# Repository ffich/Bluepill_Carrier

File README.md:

# BluePill Experimental Carrier

🧪 **BluePill Experimental Carrier** is a carrier board designed for development, testing, and rapid experimentation with the **STM32 Blue Pill (STM32F103)**.

The goal of this board is to provide a **feature-rich development platform** with integrated peripherals, industrial communication interfaces, and expansion sockets, while keeping the design clean, educational, and easy to extend.

---

## ✨ Key Features

### On-board Peripherals
- 14 × Status / debug LEDs  
- 3 × User buttons  
- 1 × Wake-up button  
- 1 × Analog potentiometer  
- **TMP102** I2C temperature sensor  
- **I²C OLED** display  
- **SPI EEPROM**  

### Communications
- **CAN bus TJA1051T3** transceiver
- **LIN Bus TJA1029T** transceiver (Configurable Master/Slave)
- **RS-485** interface with dedicated transceiver
- **USB / Serial** interface

### Security
- **Microchip ATECC608C** Cryptographic coprocessor

### Expansion Sockets
- External **DS3231 RTC Breakout** socket  
- **BME280** environmental sensor socket  

---

## 🎯 Design Philosophy

- Built for **experimentation, prototyping, and hardware/software testing**
- Well suited for:
  - Embedded development
  - Industrial and automotive communications (CAN, LIN, RS-485)
  - Sensor integration
  - Industrial and IoT applications
  - Cybersecurity

---

## 🧩 Target Audience

- Advanced makers  
- Electronics / embedded students  
- STM32 firmware developers  
- Educational labs and R&D teams  

---

## ⚠️ Disclaimer

This board is **experimental by design**.  
Layout, features, and routing may evolve as the project progresses and new tests are performed.

---

## 📜 License

Hardware and documentation are released under an open-source license.  
See the `LICENSE` file for details.

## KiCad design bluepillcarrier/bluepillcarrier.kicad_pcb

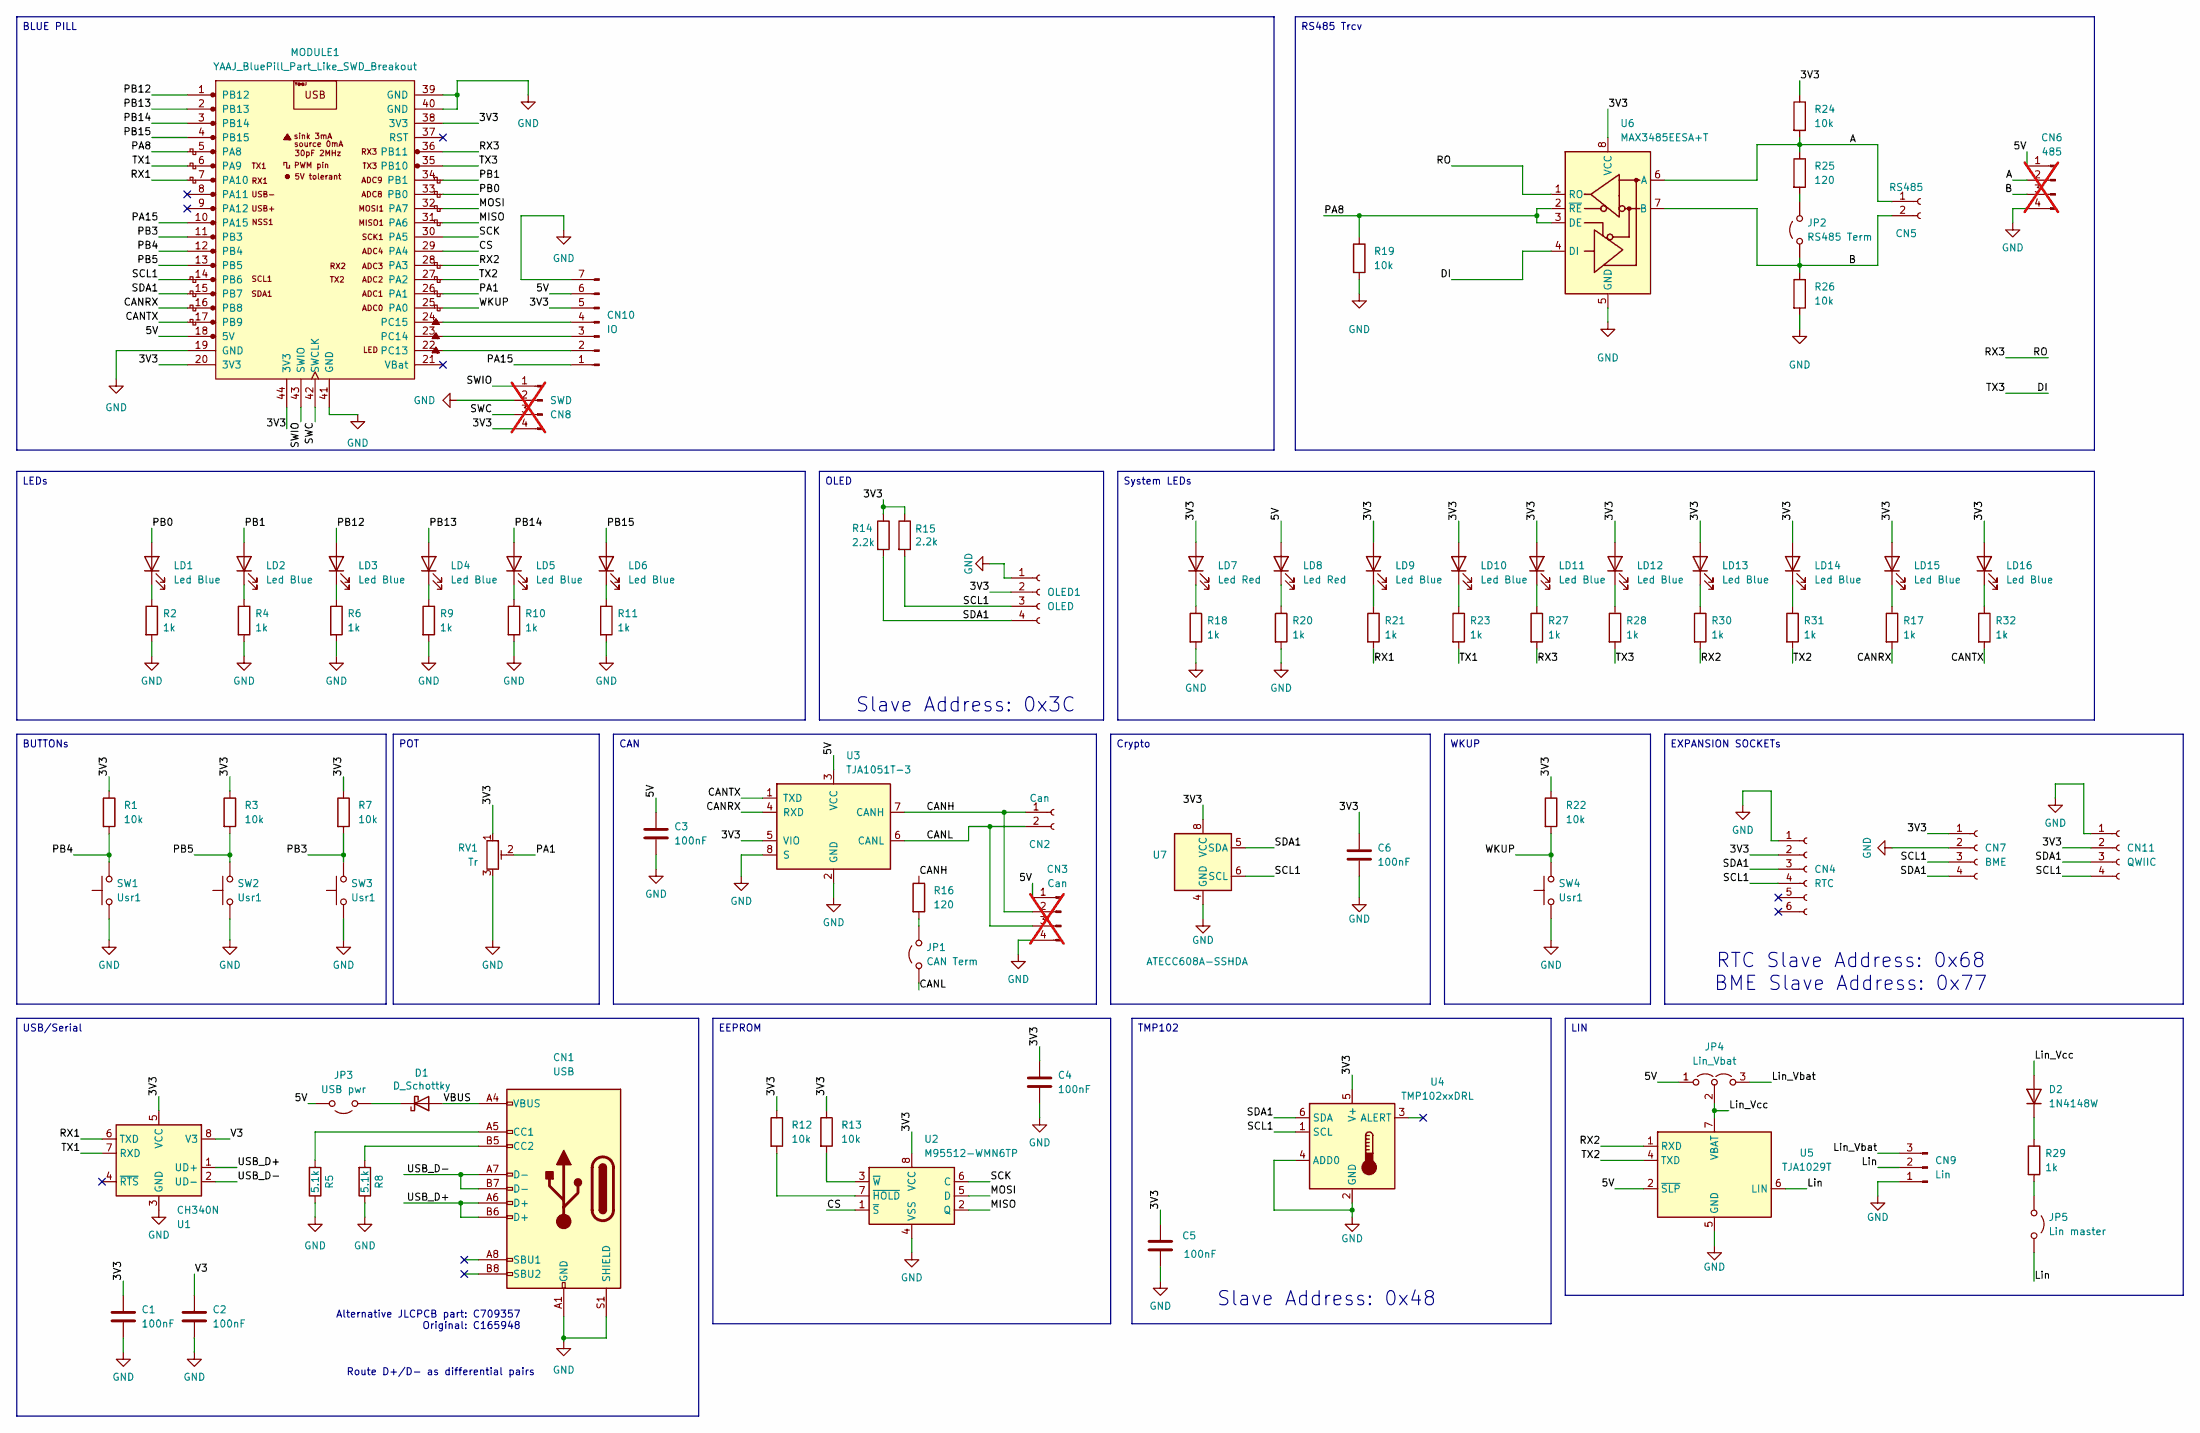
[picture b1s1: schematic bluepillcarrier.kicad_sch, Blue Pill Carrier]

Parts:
C1, C2, C3, C4, C5, C6: 100nF; C_0402_1005Metric; LCSC C155422
CN1: USB; USB_C_Receptacle_HRO_TYPE-C-31-M-12; LCSC C165948
CN2: Can; PhoenixContact_MSTBA_2,5_2-G-5,08_1x02_P5.08mm_Horizontal; LCSC C441204
CN3: Can; PinHeader_1x04_P2.54mm_Vertical; LCSC C2905435; not fitted
CN4: RTC; PinSocket_1x06_P2.54mm_Vertical; LCSC C2832269
CN5: RS485; PhoenixContact_MSTBA_2,5_2-G-5,08_1x02_P5.08mm_Horizontal; LCSC C441204
CN6: 485; PinHeader_1x04_P2.54mm_Vertical; LCSC C2905435; not fitted
CN7: BME; PinSocket_1x04_P2.54mm_Vertical; LCSC C2718488
CN8: SWD; PinHeader_1x04_P2.54mm_Vertical; not fitted
CN9: Lin; PinHeader_1x03_P2.54mm_Vertical; LCSC C49257
CN10: IO; PinSocket_1x07_P2.54mm_Vertical; LCSC C22438157
CN11: QWIIC; JST_SH_SM04B-SRSS-TB_1x04-1MP_P1.00mm_Horizontal; LCSC C160404
D1: D_Schottky; D_SMA; LCSC C412514
D2: 1N4148W; D_SOD-123; LCSC C2099
JP1: CAN Term; PinHeader_1x02_P2.54mm_Vertical; LCSC C5360898
JP2: RS485 Term; PinHeader_1x02_P2.54mm_Vertical; LCSC C5360898
JP3: USB pwr; PinHeader_1x02_P2.54mm_Vertical; LCSC C5360898
JP4: Lin_Vbat; PinHeader_1x03_P2.54mm_Vertical; LCSC C49257
JP5: Lin master; PinHeader_1x02_P2.54mm_Vertical; LCSC C5360898
LD1, LD2, LD3, LD4, LD5, LD6, LD9, LD10, LD11, LD12, LD13, LD14, LD15, LD16: Led Blue; LED_0603_1608Metric; LCSC C2288
LD7, LD8: Led Red; LED_0603_1608Metric; LCSC C2286
MODULE1: YAAJ_BluePill_Part_Like_SWD_Breakout; YAAJ_BluePill_SWD_1; LCSC C2905423
OLED1: OLED; MODULE_DM-OLED096-636; LCSC C5248080
R1, R3, R7, R12, R13, R19, R22, R24, R26: 10k; R_0402_1005Metric; LCSC C174175
R2, R4, R6, R9, R10, R11, R17, R18, R20, R21, R23, R27, R28, R29, R30, R31, R32: 1k; R_0402_1005Metric; LCSC C140196
R5, R8: 5.1k; R_0402_1005Metric; LCSC C25905
R14, R15: 2.2k; R_0603_1608Metric
R16, R25: 120; R_0603_1608Metric; LCSC C177328
RV1: Tr; Potentiometer_Bourns_3386P_Vertical; LCSC C116303
SW1, SW2, SW3, SW4: Usr1; SW_SPST_PTS810; LCSC C221895
U1: CH340N; JEITA_SOIC-8_3.9x4.9mm_P1.27mm; LCSC C2977777
U2: M95512-WMN6TP; SOIC-8_3.9x4.9mm_P1.27mm; LCSC C7567
U3: TJA1051T-3; SOIC-8_3.9x4.9mm_P1.27mm; LCSC C38695
U4: TMP102xxDRL; SOT-563; LCSC C99269
U5: TJA1029T; SOIC-8_3.9x4.9mm_P1.27mm; LCSC C194435
U6: MAX3485EESA+T; SOIC-8_3.9x4.9mm_P1.27mm; LCSC C9943
U7: ATECC608A-SSHDA; SOIC-8_3.9x4.9mm_P1.27mm; LCSC C28975195

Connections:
/3V3: C1.1, C4.1, C5.1, C6.1, CN4.2, CN7.1, CN8.4, CN10.5, CN11.2, LD7.2 (A), LD9.2 (A), LD10.2 (A), LD11.2 (A), LD12.2 (A), LD13.2 (A), LD14.2 (A), LD15.2 (A), LD16.2 (A), MODULE1.20 (3V3), MODULE1.38 (3V3), MODULE1.44 (3V3), OLED1.2, R1.1, R3.1, R7.1, R12.1, R13.1, R14.1, R15.1, R22.1, R24.1, RV1.1, U1.5 (VCC), U2.8 (VCC), U3.5 (VIO), U4.5 (V+), U6.8 (VCC), U7.8 (VCC)
/5V: C3.1, CN3.1, CN6.1, CN10.6, JP3.2 (B), JP4.1 (A), LD8.2 (A), MODULE1.18 (5V), U3.3 (VCC), U5.2 (~SLP)
/A: CN5.1, CN6.2, R24.2, R25.1, U6.6 (A)
/B: CN5.2, CN6.3, JP2.1 (A), R26.1, U6.7 (B)
/CANH: CN2.1, CN3.2, R16.1, U3.7 (CANH)
/CANL: CN2.2, CN3.3, JP1.1 (A), U3.6 (CANL)
/CANRX: MODULE1.16 (PB8), R17.2, U3.4 (RXD)
/CANTX: MODULE1.17 (PB9), R32.2, U3.1 (TXD)
/CS: MODULE1.29 (PA4), U2.1 (~S)
/DI: MODULE1.35 (PB10), R28.2, U6.4 (DI)
/Lin: CN9.2, JP5.2 (B), U5.6 (LIN)
/Lin_Vbat: CN9.3, JP4.3 (B)
/Lin_Vcc: D2.2 (A), JP4.2 (C), U5.7 (VBAT)
/MISO: MODULE1.31 (PA6), U2.2 (Q)
/MOSI: MODULE1.32 (PA7), U2.5 (D)
/PA1: MODULE1.26 (PA1), RV1.2
/PA8: MODULE1.5 (PA8), R19.1, U6.2 (~RE), U6.3 (DE)
/PA15: CN10.1, MODULE1.10 (PA15)
/PB0: LD1.2 (A), MODULE1.33 (PB0)
/PB1: LD2.2 (A), MODULE1.34 (PB1)
/PB3: MODULE1.11 (PB3), R7.2, SW3.2
/PB4: MODULE1.12 (PB4), R1.2, SW1.2
/PB5: MODULE1.13 (PB5), R3.2, SW2.2
/PB12: LD3.2 (A), MODULE1.1 (PB12)
/PB13: LD4.2 (A), MODULE1.2 (PB13)
/PB14: LD5.2 (A), MODULE1.3 (PB14)
/PB15: LD6.2 (A), MODULE1.4 (PB15)
/RO: MODULE1.36 (PB11), R27.2, U6.1 (RO)
/RX1: MODULE1.7 (PA10), R21.2, U1.6 (TXD)
/RX2: MODULE1.28 (PA3), R30.2, U5.1 (RXD)
/SCK: MODULE1.30 (PA5), U2.6 (C)
/SCL1: CN4.4, CN7.3, CN11.4, MODULE1.14 (PB6), OLED1.3, R15.2, U4.1 (SCL), U7.6 (SCL)
/SDA1: CN4.3, CN7.4, CN11.3, MODULE1.15 (PB7), OLED1.4, R14.2, U4.6 (SDA), U7.5 (SDA)
/SWC: CN8.3, MODULE1.42 (SWCLK)
/SWIO: CN8.1, MODULE1.43 (SWIO)
/TX1: MODULE1.6 (PA9), R23.2, U1.7 (RXD)
/TX2: MODULE1.27 (PA2), R31.2, U5.4 (TXD)
/USB_D+: CN1.A6 (D+), CN1.B6 (D+), U1.1 (UD+)
/USB_D-: CN1.A7 (D-), CN1.B7 (D-), U1.2 (UD-)
/V3: C2.1, U1.8 (V3)
/VBUS: CN1.A4 (VBUS), CN1.A9 (VBUS), CN1.B4 (VBUS), CN1.B9 (VBUS), D1.2 (A)
/WKUP: MODULE1.25 (PA0), R22.2, SW4.2
GND: C1.2, C2.2, C3.2, C4.2, C5.2, C6.2, CN1.A1 (GND), CN1.A12 (GND), CN1.B1 (GND), CN1.B12 (GND), CN1.S1 (SHIELD), CN3.4, CN4.1, CN6.4, CN7.2, CN8.2, CN9.1, CN10.7, CN11.1, MODULE1.19 (GND), MODULE1.39 (GND), MODULE1.40 (GND), MODULE1.41 (GND), OLED1.1, R2.2, R4.2, R5.1, R6.2, R8.1, R9.2, R10.2, R11.2, R18.2, R19.2, R20.2, R26.2, RV1.3, SW1.1, SW2.1, SW3.1, SW4.1, U1.3 (GND), U2.4 (VSS), U3.2 (GND), U3.8 (S), U4.2 (GND), U4.4 (ADD0), U5.5 (GND), U6.5 (GND), U7.4 (GND)
unnamed: CN1.A5 (CC1), R5.2
unnamed: CN1.B5 (CC2), R8.2
unnamed: CN10.2, MODULE1.22 (PC13)
unnamed: CN10.3, MODULE1.23 (PC14)
unnamed: CN10.4, MODULE1.24 (PC15)
unnamed: D1.1 (K), JP3.1 (A)
unnamed: D2.1 (K), R29.1
unnamed: JP1.2 (B), R16.2
unnamed: JP2.2 (B), R25.2
unnamed: JP5.1 (A), R29.2
unnamed: LD1.1 (K), R2.1
unnamed: LD2.1 (K), R4.1
unnamed: LD3.1 (K), R6.1
unnamed: LD4.1 (K), R9.1
unnamed: LD5.1 (K), R10.1
unnamed: LD6.1 (K), R11.1
unnamed: LD7.1 (K), R18.1
unnamed: LD8.1 (K), R20.1
unnamed: LD9.1 (K), R21.1
unnamed: LD10.1 (K), R23.1
unnamed: LD11.1 (K), R27.1
unnamed: LD12.1 (K), R28.1
unnamed: LD13.1 (K), R30.1
unnamed: LD14.1 (K), R31.1
unnamed: LD15.1 (K), R17.1
unnamed: LD16.1 (K), R32.1
unnamed: R12.2, U2.7 (~HOLD)
unnamed: R13.2, U2.3 (~W)

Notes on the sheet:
Slave Address: 0x48
Route D+/D- as differential pairs
RTC Slave Address: 0x68 BME Slave Address: 0x77
Alternative JLCPCB part: C709357 Original: C165948
Slave Address: 0x3C
WKUP
EXPANSION SOCKETs
USB/Serial
RS485 Trcv
LIN
BUTTONs
BLUE PILL
System LEDs
EEPROM
CAN
LEDs
Crypto
POT
TMP102
OLED

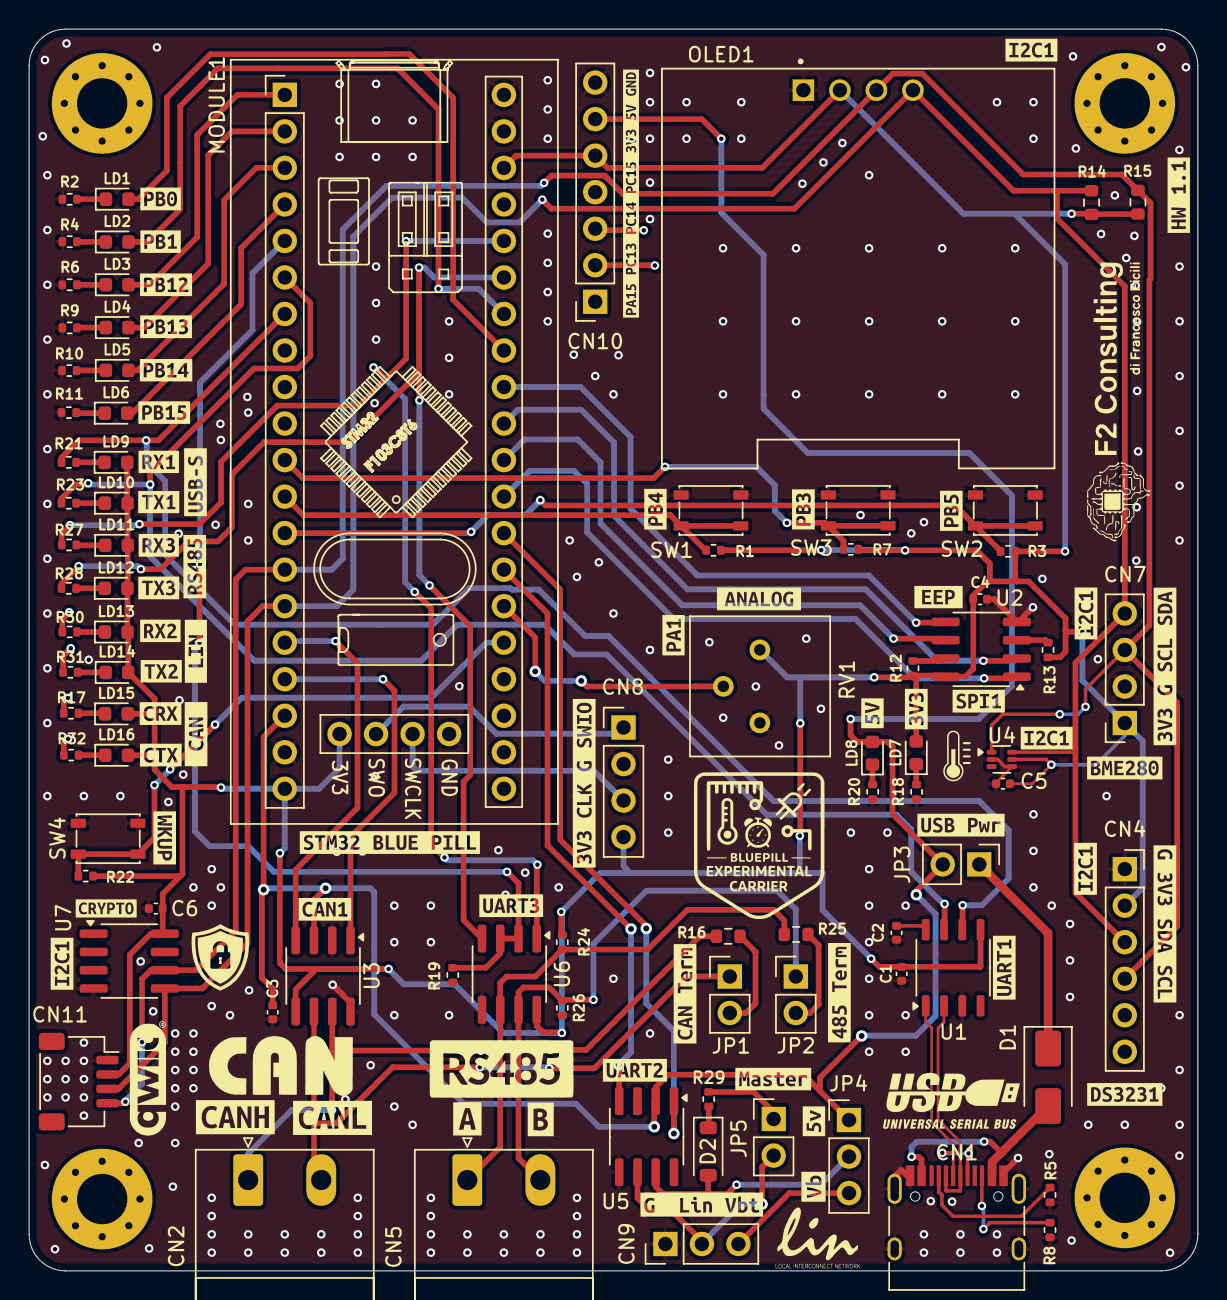
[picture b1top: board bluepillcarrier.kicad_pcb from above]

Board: 4 copper layers, 81.3 x 86.4 mm, 141 parts (0 on the bottom side), 71 nets.

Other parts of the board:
kibuzzard-695AB37B: G***; kibuzzard-695AB37B
kibuzzard-695AB373: G***; kibuzzard-695AB373
kibuzzard-696A2AD8: G***; kibuzzard-696A2AD8
kibuzzard-696A4D9E: G***; kibuzzard-696A4D9E
kibuzzard-696A4D49: G***; kibuzzard-696A4D49
kibuzzard-696A4D50: G***; kibuzzard-696A4D50
kibuzzard-696A23BE: G***; kibuzzard-696A23BE
kibuzzard-696A233A: G***; kibuzzard-696A233A
kibuzzard-696A237E: G***; kibuzzard-696A237E
kibuzzard-696A2374: G***; kibuzzard-696A2374
kibuzzard-69594BD1: G***; kibuzzard-69594BD1
kibuzzard-69594BE1: G***; kibuzzard-69594BE1
kibuzzard-69594BEF: G***; kibuzzard-69594BEF
kibuzzard-69594BFB: G***; kibuzzard-69594BFB
kibuzzard-69594C3C: G***; kibuzzard-69594C3C
kibuzzard-69594C6D: G***; kibuzzard-69594C6D
kibuzzard-69594C8A: G***; kibuzzard-69594C8A
kibuzzard-69594C8F: G***; kibuzzard-69594C8F
kibuzzard-69594C11: G***; kibuzzard-69594C11
kibuzzard-69594C18: G***; kibuzzard-69594C18
kibuzzard-69594C37: G***; kibuzzard-69594C37
kibuzzard-69594C59: G***; kibuzzard-69594C59
kibuzzard-69594C68: G***; kibuzzard-69594C68
kibuzzard-69594C94: G***; kibuzzard-69594C94
kibuzzard-69594CA2: G***; kibuzzard-69594CA2
kibuzzard-69594D1B: G***; kibuzzard-69594D1B
kibuzzard-69594D2D: G***; kibuzzard-69594D2D
kibuzzard-69594D3A: G***; kibuzzard-69594D3A
kibuzzard-69594D5C: G***; kibuzzard-69594D5C
kibuzzard-69594D06: G***; kibuzzard-69594D06
kibuzzard-69594D9E: G***; kibuzzard-69594D9E
kibuzzard-69594D45: G***; kibuzzard-69594D45
kibuzzard-69594D50: G***; kibuzzard-69594D50
kibuzzard-69594D57: G***; kibuzzard-69594D57
kibuzzard-69594D63: G***; kibuzzard-69594D63
kibuzzard-69594DB5: G***; kibuzzard-69594DB5
kibuzzard-69594DEB, kibuzzard-69594DEB#2, kibuzzard-69594DEB#3, kibuzzard-69594DEB#4, kibuzzard-69594DEB#5: G***; kibuzzard-69594DEB
kibuzzard-69594E2D: G***; kibuzzard-69594E2D
kibuzzard-69594E7B: G***; kibuzzard-69594E7B
kibuzzard-69636EB7: G***; kibuzzard-69636EB7
kibuzzard-69636ED7: G***; kibuzzard-69636ED7
kibuzzard-69636EE0: G***; kibuzzard-69636EE0
kibuzzard-69636EED: G***; kibuzzard-69636EED
kibuzzard-69908B33: G***; kibuzzard-69908B33
kibuzzard-69908F2A: G***; kibuzzard-69908F2A
kibuzzard-69908F16: G***; kibuzzard-69908F16
kibuzzard-69908F24: G***; kibuzzard-69908F24
kibuzzard-69909E2E: G***; kibuzzard-69909E2E
kibuzzard-694153A1: G***; kibuzzard-694153A1
kibuzzard-694153B4: G***; kibuzzard-694153B4
kibuzzard-69415277: G***; kibuzzard-69415277
kibuzzard-69415288: G***; kibuzzard-69415288
kibuzzard-69909054: G***; kibuzzard-69909054

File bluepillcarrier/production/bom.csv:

Designator,Footprint,Quantity,Value,LCSC Part #
"C1, C2, C3, C4, C5, C6",0402,6,100nF,C155422
CN1,USB_C_Receptacle_HRO_TYPE-C-31-M-12,1,USB,C165948
CN10,PinSocket_1x07_P2.54mm_Vertical,1,IO,C22438157
CN11,JST_SH_SM04B-SRSS-TB_1x04-1MP_P1.00mm_Horizontal,1,QWIIC,C160404
CN2,"PhoenixContact_MSTBA_2,5_2-G-5,08_1x02_P5.08mm_Horizontal",1,Can,C441204
CN4,PinSocket_1x06_P2.54mm_Vertical,1,RTC,C2832269
CN5,"PhoenixContact_MSTBA_2,5_2-G-5,08_1x02_P5.08mm_Horizontal",1,RS485,C441204
CN7,PinSocket_1x04_P2.54mm_Vertical,1,BME,C2718488
CN9,PinHeader_1x03_P2.54mm_Vertical,1,Lin,C49257
D1,D_SMA,1,D_Schottky,C412514
D2,D_SOD-123,1,1N4148W,C2099
JP1,PinHeader_1x02_P2.54mm_Vertical,1,CAN Term,C5360898
JP2,PinHeader_1x02_P2.54mm_Vertical,1,RS485 Term,C5360898
JP3,PinHeader_1x02_P2.54mm_Vertical,1,USB pwr,C5360898
JP4,PinHeader_1x03_P2.54mm_Vertical,1,Lin_Vbat,C49257
JP5,PinHeader_1x02_P2.54mm_Vertical,1,Lin master,C5360898
"LD1, LD10, LD11, LD12, LD13, LD14, LD15, LD16, LD2, LD3, LD4, LD5, LD6, LD9",0603,14,Led Blue,C2288
"LD7, LD8",0603,2,Led Red,C2286
MODULE1A,YAAJ_BluePill_SWD_1,1,YAAJ_BluePill_Part_Like_SWD_Breakout,C2905423
MODULE1B,YAAJ_BluePill_SWD_1,1,YAAJ_BluePill_Part_Like_SWD_Breakout,C2905423
OLED1,MODULE_DM-OLED096-636,1,OLED,C5248080
"R1, R12, R13, R19, R22, R24, R26, R3, R7",0402,9,10k,C174175
"R10, R11, R17, R18, R2, R20, R21, R23, R27, R28, R29, R30, R31, R32, R4, R6, R9",0402,17,1k,C140196
"R14, R15",0603,2,2.2k,
"R16, R25",0603,2,120,C177328
"R5, R8",0402,2,5.1k,C25905
RV1,Potentiometer_Bourns_3386P_Vertical,1,Tr,C116303
"SW1, SW2, SW3, SW4",SW_SPST_PTS810,4,Usr1,C221895
U1,JEITA_SOIC-8_3.9x4.9mm_P1.27mm,1,CH340N,C2977777
U2,SOIC-8_3.9x4.9mm_P1.27mm,1,M95512-WMN6TP,C7567
U3,SOIC-8_3.9x4.9mm_P1.27mm,1,TJA1051T-3,C38695
U4,SOT-563,1,TMP102xxDRL,C99269
U5,SOIC-8_3.9x4.9mm_P1.27mm,1,TJA1029T,C194435
U6,SOIC-8_3.9x4.9mm_P1.27mm,1,MAX3485EESA+T,C9943
U7,SOIC-8_3.9x4.9mm_P1.27mm,1,ATECC608A-SSHDA,C28975195

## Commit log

2025-12-16 Added carrier project
2025-12-16 Update README.md
    minor
2025-12-17 Some updates and fixes
2025-12-17 added bom
2025-12-17 minor
2026-01-03 Fixes: - Corrected OLED footprint - Green led resistor set to 1k - Updated all the labels to 1mm for better visibility - Moved trimmer a bit below to save a bit of space for buttons
2026-01-08 Some additional fixes
2026-01-11 some updates
2026-01-15 Final design without LIN
2026-01-15 - changed temperature sensor
2026-01-18 some minor modifications
2026-02-02 Added LIN Bus based on NXP Lin transceiver TJA1021
2026-03-20 Updated schematic and ibom
2026-04-21 Some changes/fixes: -Fixed error on interface - Added TX/RX LEDs for CAN - Replaces Buzzer with ATECC608C crypto chip - Added QWIIC
